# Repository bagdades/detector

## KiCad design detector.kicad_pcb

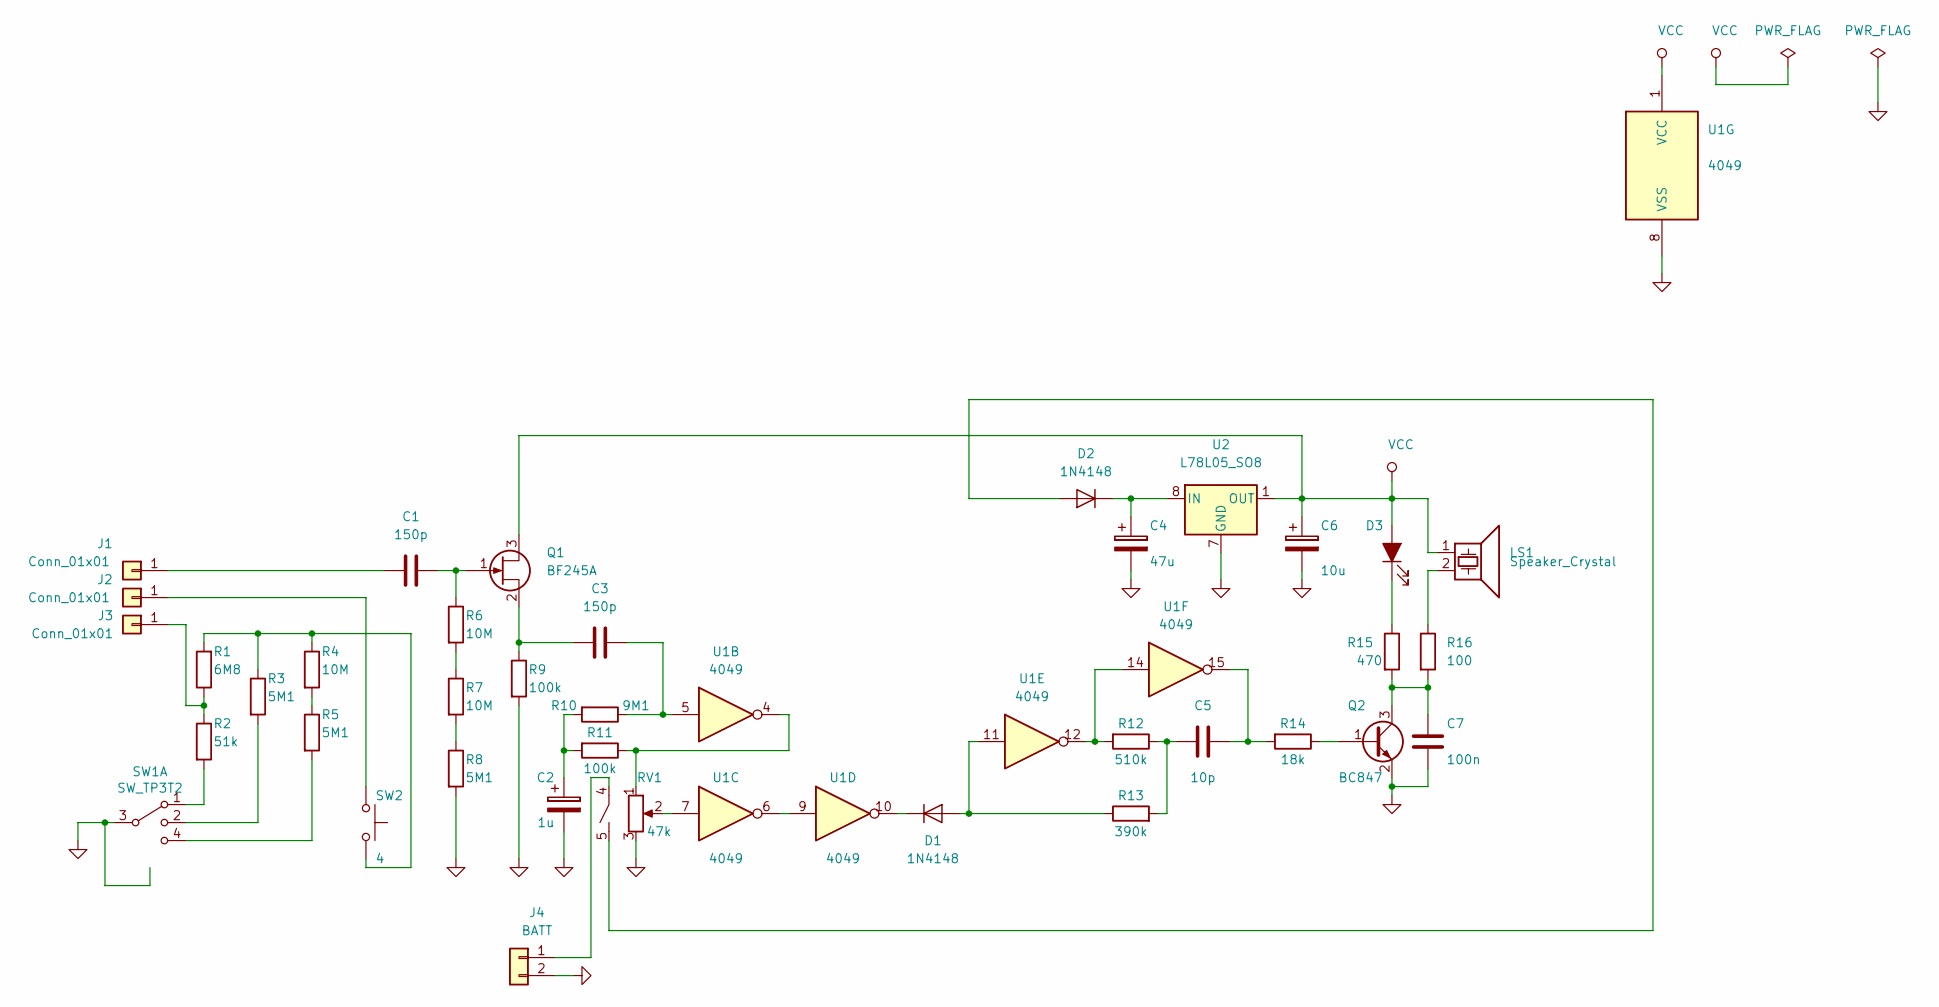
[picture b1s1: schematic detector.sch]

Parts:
C1, C3: 150p; C_0603_1608Metric
C2: 1u; CP_EIA-2012-12_Kemet-R
C4: 47u; CP_EIA-3528-21_Kemet-B
C5: 10p; C_0603_1608Metric
C6: 10u; CP_EIA-3528-21_Kemet-B
C7: 100n; C_0603_1608Metric
D1, D2: 1N4148; D_DO-35_SOD27_P7.62mm_Horizontal
D3: LED_ALT; LED_D3.0mm
J1, J2, J3: Conn_01x01; PinHeader_1x01_P2.54mm_Vertical
J4: BATT; PinHeader_1x02_P2.54mm_Vertical
LS1: Speaker_Crystal; PinHeader_1x02_P2.54mm_Vertical
Q1: BF245A; TO-92L
Q2: BC847; SOT-23
R1: 6M8; R_0805_2012Metric
R2: 51k; R_0603_1608Metric
R3, R5, R8: 5M1; R_0805_2012Metric
R4, R6, R7: 10M; R_0805_2012Metric
R9, R11: 100k; R_0603_1608Metric
R10: 9M1; R_0805_2012Metric
R12: 510k; R_0603_1608Metric
R13: 390k; R_0603_1608Metric
R14: 18k; R_0603_1608Metric
R15: 470; R_0603_1608Metric
R16: 100; R_0603_1608Metric
RV1: 47k; Pot
SW1: SW_TP3T2; SW_SP3T2
SW2: 4; SW_PUSH_6mm_H8mm
U1: 4049; SOIC-16_3.9x9.9mm_P1.27mm
U2: L78L05_SO8; SOIC-8_3.9x4.9mm_P1.27mm

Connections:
GND: C2.2, C4.2, C6.2, C7.1, J4.2, Q2.2 (E), R8.2, R9.2, RV1.3, SW1.3, SW1.9 (Shield), SW1.10 (Shield), U1.8 (VSS), U2.2 (GND), U2.3 (GND), U2.6 (GND), U2.7 (GND)
unnamed: C1.1, Q1.1 (G), R6.1
unnamed: C1.2, J1.1
unnamed: C2.1, R10.2, R11.2
unnamed: C3.1, R10.1, U1.5
unnamed: C3.2, Q1.2 (S), R9.1
unnamed: C4.1, D2.1 (K), U2.8 (IN)
unnamed: C5.1, R14.2, U1.15
unnamed: C5.2, R12.1, R13.2
unnamed: C7.2, Q2.3 (C), R15.2, R16.2
unnamed: D1.1 (K), U1.10
unnamed: D1.2 (A), R13.1, U1.11
unnamed: D2.2 (A), RV1.5
unnamed: D3.1 (K), R15.1
unnamed: J2.1, SW2.1
unnamed: J3.1, R1.1, R2.1
unnamed: J4.1, RV1.4
unnamed: LS1.2, R16.1
unnamed: Q2.1 (B), R14.1
unnamed: R1.2, R3.1, R4.1, SW2.2
unnamed: R2.2, SW1.1
unnamed: R3.2, SW1.2
unnamed: R4.2, R5.1
unnamed: R5.2, SW1.4
unnamed: R6.2, R7.1
unnamed: R7.2, R8.1
unnamed: R11.1, RV1.1, U1.4
unnamed: R12.2, U1.12, U1.14
unnamed: RV1.2, U1.7
unnamed: U1.6, U1.9
VCC: C6.1, D3.2 (A), LS1.1, Q1.3 (D), U1.1 (VCC), U2.1 (OUT)

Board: 2 copper layers, 38 parts (0 on the bottom side), 31 nets, no tracks yet.

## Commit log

2019-01-27 Create all footprints
